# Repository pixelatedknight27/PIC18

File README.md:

# A PIC18 development board
### Based off of Professor Felix Pinai's ECE3301L board

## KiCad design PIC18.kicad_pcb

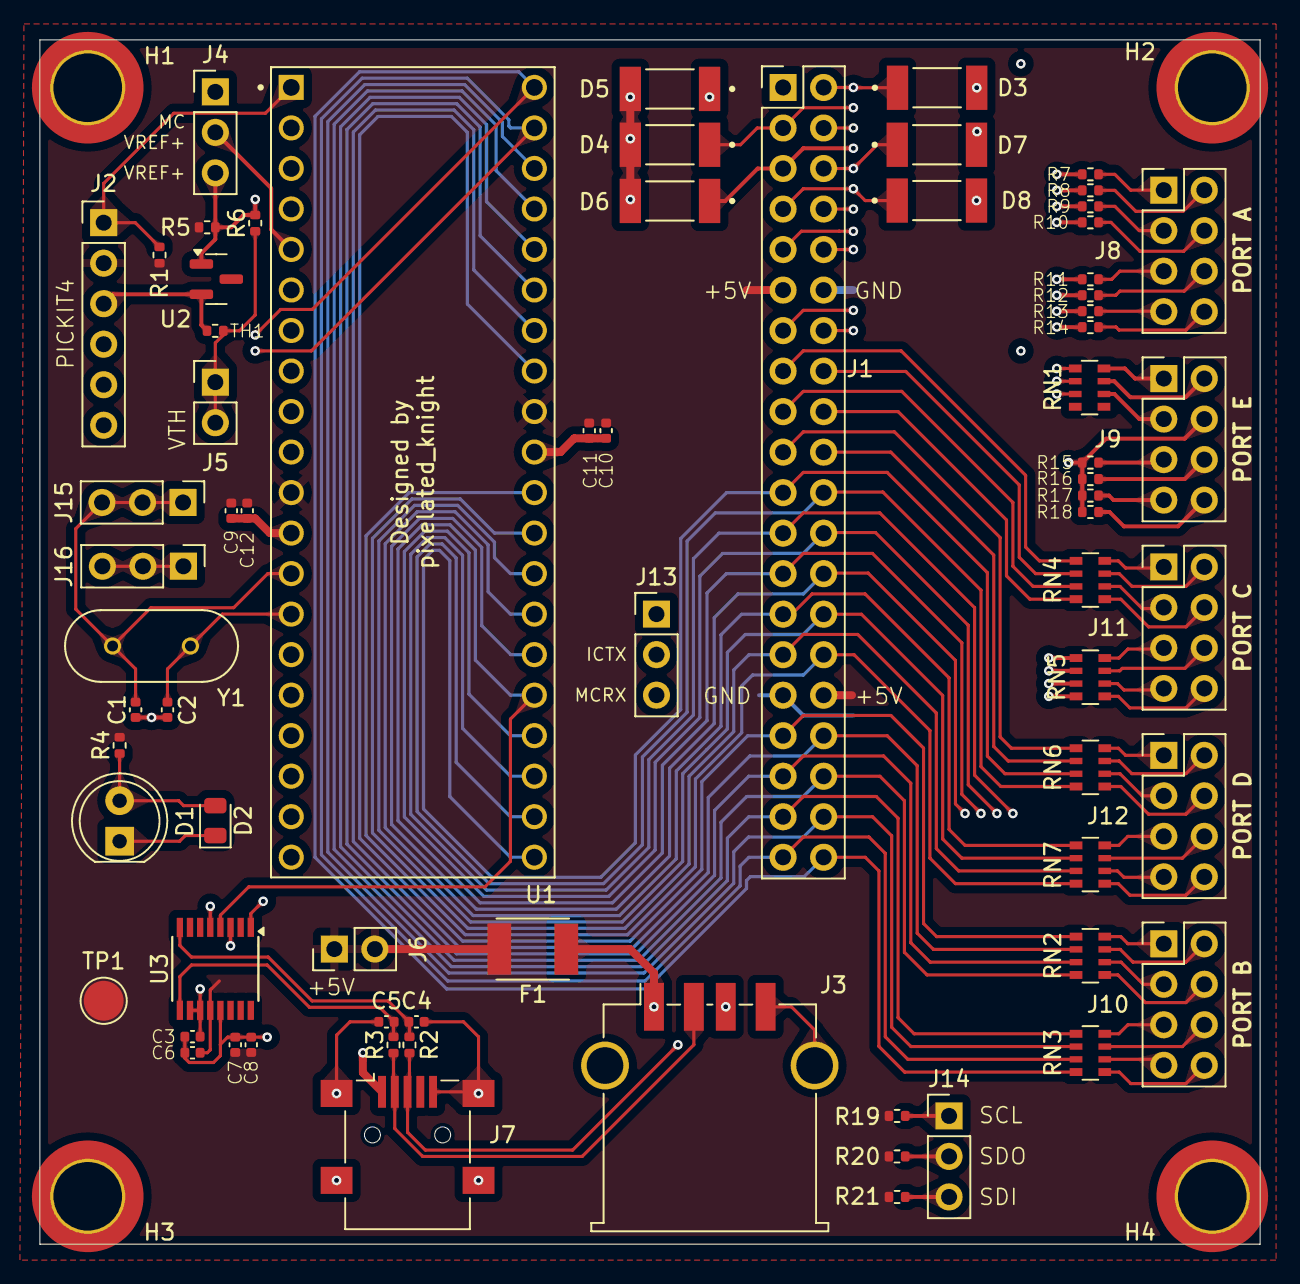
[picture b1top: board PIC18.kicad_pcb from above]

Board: 4 copper layers, 76.5 x 75.5 mm, 75 parts (0 on the bottom side), 87 nets.

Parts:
C1, C2: 22pF; C_0402_1005Metric
C3, C6: 100nF; C_0402_1005Metric
C4, C5: 47pf; C_0402_1005Metric
C7: 4.7u; C_0402_1005Metric
C8, C10, C12: 100nf; C_0402_1005Metric
C9, C11: 1uf; C_0402_1005Metric
D1: LED; LED_D5.0mm
D2: LED; LED_0805_2012Metric
D3, D4, D5, D6, D7, D8: ZMM5V1; DIOMELF5124N
F1: MF-MSMF200-2; FUSER_MF-MSMF200-2
H1, H2, H3, H4: MountingHole_Pad; MountingHole_4.3mm_M4_ISO14580_Pad_TopBottom
J1: Conn_02x20_Odd_Even; PinSocket_2x20_Counter_Clockwise_P2.54mm_Vertical
J2: Conn_01x06; PinHeader_1x06_P2.54mm_Vertical
J3: USB_A; USB_A_TE_292303-7_Horizontal
J4, J13, J14, J15, J16: Conn_01x03; PinHeader_1x03_P2.54mm_Vertical
J5, J6: Conn_01x02; PinHeader_1x02_P2.54mm_Vertical
J7: USB_OTG; USB_Mini-B_Lumberg_2486_01_Horizontal
J8: Port A; PinHeader_2x04_P2.54mm_Vertical_Red
J9: Port E; PinHeader_2x04_P2.54mm_Vertical_Green
J10: Port B; PinHeader_2x04_P2.54mm_Vertical_Yellow
J11: Port C; PinHeader_2x04_P2.54mm_Vertical_Blue
J12: Port D; PinHeader_2x04_P2.54mm_Vertical_White
R1: 10K; R_0402_1005Metric
R2, R3, R5: 33; R_0402_1005Metric
R4, R6, R7, R8, R9, R10, R11, R12, R13, R14: 220; R_0402_1005Metric
R15: 100; R_0402_1005Metric
R16: 1k; R_0402_1005Metric
R17, R19, R20, R21: 10k; R_0402_1005Metric
R18: 100k; R_0402_1005Metric
RN1, RN2, RN3, RN4, RN5, RN6, RN7: 220; R_Array_Convex_4x0603
TH1: 10k; R_0402_1005Metric
TP1: TestPoint; TestPoint_Pad_D2.5mm
U1: PIC18F4620; AMPHENOL_DILB40P-223TLF
U2: LM4040DBZ-4.1; SOT-23
U3: FT230XS; SSOP-16_3.9x4.9mm_P0.635mm
Y1: 8 MHz; XTAL_HC49P488W43L1085T450H368

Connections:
/*MCLR/VPP/RE3: J1.1, J2.1, R1.2, U1.1 (*MCLR/VPP/RE3)
/OSC1/CLKI/RA7: C1.2, J1.13, J15.1, J15.2, J15.3, R13.1, U1.13 (OSC1/CLKI/RA7), Y1.2
/OSC2/CLKO/RA6: C2.2, J1.14, J16.1, J16.2, J16.3, R14.1, U1.14 (OSC2/CLKO/RA6), Y1.1
/RA0/AN0: D3.1 (K), J1.2, R7.1, U1.2 (RA0/AN0)
/RA1/AN1: D4.1 (K), J1.3, R8.1, U1.3 (RA1/AN1)
/RA2/AN2/VREF-/CVREF: D5.1 (K), J1.4, R9.1, U1.4 (RA2/AN2/VREF-/CVREF)
/RA3/AN3/VREF+: D6.1 (K), J1.5, J4.2, R10.1, U1.5 (RA3/AN3/VREF+)
/RA4/T0CKI/C1OUT: D7.1 (K), J1.6, R11.1, U1.6 (RA4/T0CKI/C1OUT)
/RA5/AN4/SS*/HLVDIN/C2OUT: D8.1 (K), J1.7, R12.1, U1.7 (RA5/AN4/SS*/HLVDIN/C2OUT)
/RB0/INT0/FLT0/AN12: J1.33, RN2.5 (R4.2), U1.33 (RB0/INT0/FLT0/AN12)
/RB1/INT1/AN10: J1.34, RN2.6 (R3.2), U1.34 (RB1/INT1/AN10)
/RB2/INT2/AN8: J1.35, RN2.7 (R2.2), U1.35 (RB2/INT2/AN8)
/RB3/AN9/CCP2(1): J1.36, RN2.8 (R1.2), U1.36 (RB3/AN9/CCP2(1))
/RB4/KBI0/AN11: J1.37, RN3.5 (R4.2), U1.37 (RB4/KBI0/AN11)
/RB5/KBI1/PGM: J1.38, RN3.6 (R3.2), U1.38 (RB5/KBI1/PGM)
/RB6/KBI2/PGC: J1.39, J2.5, RN3.7 (R2.2), U1.39 (RB6/KBI2/PGC)
/RB7/KBI3/PGD: J1.40, J2.4, RN3.8 (R1.2), U1.40 (RB7/KBI3/PGD)
/RC0/T1OSO/T13CKI: J1.15, RN4.5 (R4.2), U1.15 (RC0/T1OSO/T13CKI)
/RC1/T1OSI/CCP2(1): J1.16, RN4.6 (R3.2), U1.16 (RC1/T1OSI/CCP2(1))
/RC2/CCP1/P1A: J1.17, RN4.7 (R2.2), U1.17 (RC2/CCP1/P1A)
/RC3/SCK/SCL: J1.18, J14.1, R19.2, RN4.8 (R1.2), U1.18 (RC3/SCK/SCL)
/RC4/SDI/SDA: J1.23, J14.3, R21.2, RN5.5 (R4.2), U1.23 (RC4/SDI/SDA)
/RC5/SDO: J1.24, J14.2, R20.2, RN5.6 (R3.2), U1.24 (RC5/SDO)
/RC6/TX/CK: J1.25, RN5.7 (R2.2), U1.25 (RC6/TX/CK), U3.4 (RXD)
/RC7/RX/DT: J1.26, J13.3, RN5.8 (R1.2), U1.26 (RC7/RX/DT)
/RD0/PSP0: J1.19, RN6.5 (R4.2), U1.19 (RD0/PSP0)
/RD1/PSP1: J1.20, RN6.6 (R3.2), U1.20 (RD1/PSP1)
/RD2/PSP2: J1.21, RN6.7 (R2.2), U1.21 (RD2/PSP2)
/RD3/PSP3: J1.22, RN6.8 (R1.2), U1.22 (RD3/PSP3)
/RD4/PSP4: J1.27, RN7.5 (R4.2), U1.27 (RD4/PSP4)
/RD5/PSP5/P1B: J1.28, RN7.6 (R3.2), U1.28 (RD5/PSP5/P1B)
/RD6/PSP6/P1C: J1.29, RN7.7 (R2.2), U1.29 (RD6/PSP6/P1C)
/RD7/PSP7/P1D: J1.30, RN7.8 (R1.2), U1.30 (RD7/PSP7/P1D)
/RE0/RD*/AN5: J1.8, RN1.5 (R4.2), U1.8 (RE0/RD*/AN5)
/RE1/WR*/AN6: J1.9, RN1.6 (R3.2), U1.9 (RE1/WR*/AN6)
/RE2/CS*/AN7: J1.10, RN1.7 (R2.2), U1.10 (RE2/CS*/AN7)
/TXD: J13.2, U3.1 (TXD)
/VREF+: J4.3, J9.4, R5.2, R6.2, R15.1, R16.1, R17.1, R18.1, U2.1 (K)
/VTHERM: J5.1, J5.2, R6.1, TH1.1
GND: C1.1, C2.1, C3.2, C4.2, C5.2, C6.2, C7.2, C8.1, C9.1, C10.1, C11.1, C12.1, D1.1 (K), D2.1 (K), D3.2 (A), D4.2 (A), D5.2 (A), D6.2 (A), D7.2 (A), D8.2 (A), H1.1, H2.1, H3.1, H4.1, J1.12, J1.31, J2.3, J3.4 (GND), J3.5 (Shield), J7.5 (GND), J7.6 (Shield), TH1.2, U1.12 (VSS), U1.31 (VSS), U2.2 (A), U3.5 (GND), U3.13 (GND)
unnamed: D1.2 (A), D2.2 (A), R4.1
unnamed: J3.3 (D+), J7.3 (D+), R2.1
unnamed: J3.2 (D-), J7.2 (D-), R3.1
unnamed: F1.1, J3.1 (VBUS), J7.1 (VBUS)
unnamed: J8.1, R7.2
unnamed: J8.2, R8.2
unnamed: J8.3, R9.2
unnamed: J8.4, R10.2
unnamed: J8.5, R11.2
unnamed: J8.6, R12.2
unnamed: J8.7, R13.2
unnamed: J8.8, R14.2
unnamed: J9.1, RN1.4 (R4.1)
unnamed: J9.2, RN1.3 (R3.1)
unnamed: J9.3, RN1.2 (R2.1)
unnamed: J9.5, R15.2
unnamed: J9.6, R16.2
unnamed: J9.7, R17.2
unnamed: J9.8, R18.2
unnamed: J10.1, RN2.4 (R4.1)
unnamed: J10.2, RN2.3 (R3.1)
unnamed: J10.3, RN2.2 (R2.1)
unnamed: J10.4, RN2.1 (R1.1)
unnamed: J10.5, RN3.4 (R4.1)
unnamed: J10.6, RN3.3 (R3.1)
unnamed: J10.7, RN3.2 (R2.1)
unnamed: J10.8, RN3.1 (R1.1)
unnamed: J11.1, RN4.4 (R4.1)
unnamed: J11.2, RN4.3 (R3.1)
unnamed: J11.3, RN4.2 (R2.1)
unnamed: J11.4, RN4.1 (R1.1)
unnamed: J11.5, RN5.4 (R4.1)
unnamed: J11.6, RN5.3 (R3.1)
unnamed: J11.7, RN5.2 (R2.1)
unnamed: J11.8, RN5.1 (R1.1)
unnamed: J12.1, RN6.4 (R4.1)
unnamed: J12.2, RN6.3 (R3.1)
unnamed: J12.3, RN6.2 (R2.1)
unnamed: J12.4, RN6.1 (R1.1)
unnamed: J12.5, RN7.4 (R4.1)
unnamed: J12.6, RN7.3 (R3.1)
unnamed: J12.7, RN7.2 (R2.1)
unnamed: J12.8, RN7.1 (R1.1)
unnamed: C3.1, U3.3 (VCCIO), U3.10 (3V3OUT), U3.11 (~RESET)
unnamed: C5.1, R3.2, U3.9 (USBDM)
unnamed: C4.1, R2.2, U3.8 (USBDP)
VCC: C6.1, C7.1, C8.2, C9.2, C10.2, C11.2, C12.2, F1.2, J1.11, J1.32, J2.2, J6.1, J6.2, R1.1, R4.2, R5.1, R19.1, R20.1, R21.1, TP1.1, U1.11 (VDD), U1.32 (VDD), U3.12 (VCC)

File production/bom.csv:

Designator,Footprint,Quantity,Value,LCSC Part #
"C1, C2",0402,2,22pF,
"C10, C12, C3, C6, C8",0402,5,100nf,
"C11, C9",0402,2,1uf,
"C4, C5",0402,2,47pf,
C7,0402,1,4.7u,
D2,0805,1,LED,
"D3, D4, D5, D6, D7, D8",DIOMELF5124N,6,ZMM5V1,
F1,FUSER_MF-MSMF200-2,1,MF-MSMF200-2,
J1,PinHeader_2x20_P2.54mm_Vertical,1,Conn_02x20_Odd_Even,
J10,PinHeader_2x04_P2.54mm_Vertical_Yellow,1,Port B,
J11,PinHeader_2x04_P2.54mm_Vertical_Blue,1,Port C,
J12,PinHeader_2x04_P2.54mm_Vertical_White,1,Port D,
"J13, J14, J4",PinHeader_1x03_P2.54mm_Vertical,3,Conn_01x03,
J2,PinHeader_1x06_P2.54mm_Vertical,1,Conn_01x06,
J3,USB_A_TE_292303-7_Horizontal,1,USB_A,
"J5, J6",PinHeader_1x02_P2.54mm_Vertical,2,Conn_01x02,
J7,USB_Mini-B_Lumberg_2486_01_Horizontal,1,USB_OTG,
J8,PinHeader_2x04_P2.54mm_Vertical_Red,1,Port A,
J9,PinHeader_2x04_P2.54mm_Vertical_Green,1,Port E,
"R1, R17, R19, R20, R21, TH1",0402,6,10K,
"R10, R11, R12, R13, R14, R4, R6, R7, R8, R9",0402,10,220,
R15,0402,1,100,
R16,0402,1,1k,
R18,0402,1,100k,
"R2, R3, R5",0402,3,33,
"RN1, RN2, RN3, RN4, RN5, RN6, RN7",R_Array_Convex_4x0603,7,220,
TP1,TestPoint_Pad_D2.5mm,1,TestPoint,
U1,AMPHENOL_DILB40P-223TLF,1,PIC18F4620,
U2,SOT-23,1,LM4040DBZ-4.1,
U3,SSOP-16_3.9x4.9mm_P0.635mm,1,FT230XS,
Y1,XTAL_HC49P488W43L1085T450H368,1,8 MHz,

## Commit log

2024-06-22 footprint and step assignment
2024-06-23 More footprint assignments
2024-06-23 yet more footprint assignment
2024-06-23 added Zener and colored pin headers
2024-06-29 Updated schematic
2024-06-30 finishing touches on schematic
2024-06-30 More updates
2024-06-30 lots of changes
2024-06-30 Routing
2024-06-30 Placement
2024-06-30 Schematic edit
2024-07-01 Silkscreen edits
2024-07-01 Back to 2 layers
2024-07-01 Header routing
2024-07-01 More routing
2024-07-01 Autosave
2024-07-04 PCB edit
2024-07-04 lots
2024-07-05 neat
2024-07-05 Header Wiring
2024-07-05 All main wiring done
2024-07-05 Edited PCB
2024-07-07 JLCPCB parody edits
2024-07-10 more jlcpcb parody
2024-07-10 prod
2024-07-12 Changed main pin header to pin socket
2024-08-14 fixed port B
